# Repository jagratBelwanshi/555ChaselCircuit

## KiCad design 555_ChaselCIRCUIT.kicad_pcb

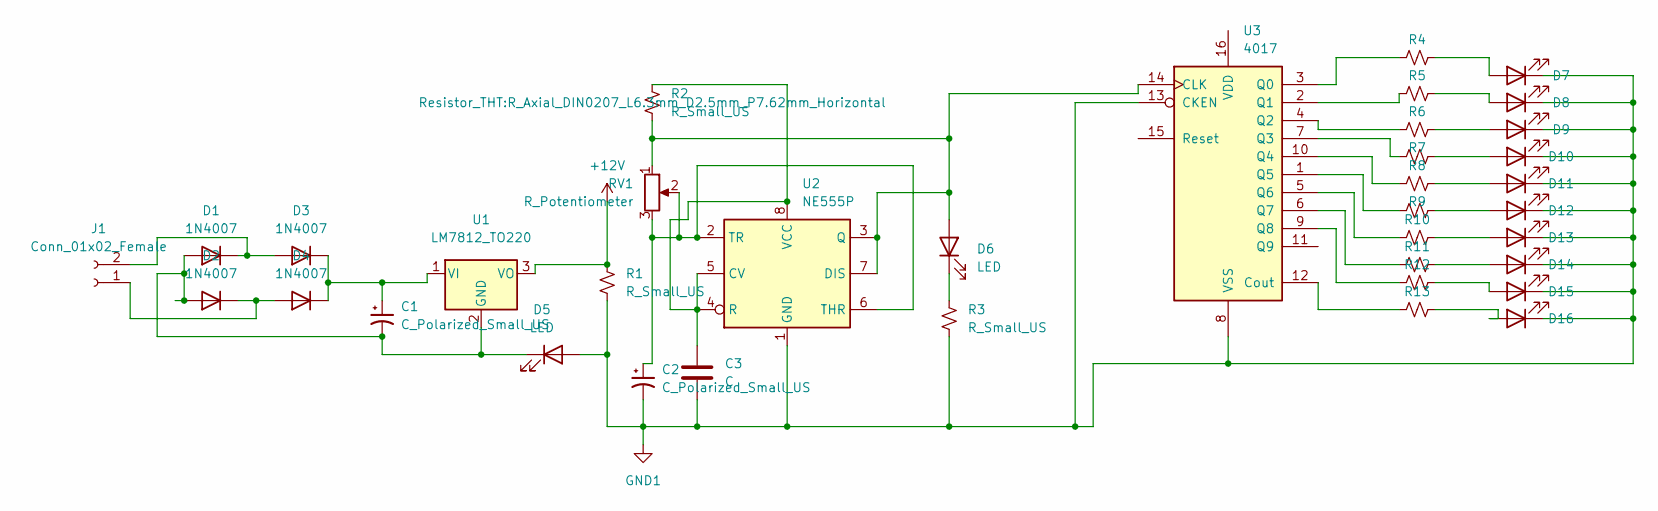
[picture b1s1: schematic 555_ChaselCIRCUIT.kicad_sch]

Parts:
C1: C_Polarized_Small_US
C2: C_Polarized_Small_US; CP_Radial_D8.0mm_P2.50mm
C3: C
D1, D2, D3, D4: 1N4007; D_DO-41_SOD81_P10.16mm_Horizontal
D5, D7, D8, D9, D10, D11, D12, D13, D14: LED; LED_D4.0mm
D6, D15, D16: LED
J1: Conn_01x02_Female
R1, R12: R_Small_US; R_Axial_DIN0204_L3.6mm_D1.6mm_P7.62mm_Horizontal
R2, R3: R_Small_US; R_Axial_DIN0207_L6.3mm_D2.5mm_P7.62mm_Horizontal
R4, R5, R6, R7, R8, R9, R10, R11, R13: R_Small_US
RV1: R_Potentiometer
U1: LM7812_TO220; TO-220-3_Vertical
U2: NE555P; DIP-8_W7.62mm
U3: 4017

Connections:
+12V: R1.1, U1.3 (VO)
GND1: C2.2, C3.2, D5.2 (A), D7.1 (K), D8.1 (K), D9.1 (K), D10.1 (K), D11.1 (K), D12.1 (K), D13.1 (K), D14.1 (K), D15.1 (K), D16.1 (K), R1.2, R3.2, U2.1 (GND), U3.8 (VSS), U3.13 (CKEN)
unnamed: C1.1, D3.1 (K), D4.1 (K), U1.1 (VI)
unnamed: C1.2, D1.2 (A), D2.2 (A), D5.1 (K), U1.2 (GND)
unnamed: C2.1, RV1.2, RV1.3, U2.2 (TR), U2.6 (THR)
unnamed: C3.1, R2.1, U2.4 (R), U2.5 (CV), U2.8 (VCC)
unnamed: D1.1 (K), D3.2 (A), J1.2
unnamed: D2.1 (K), D4.2 (A), J1.1
unnamed: D6.1 (K), R3.1
unnamed: D6.2 (A), R2.2, RV1.1, U2.3 (Q), U2.7 (DIS), U3.14 (CLK)
unnamed: D7.2 (A), R4.2
unnamed: D8.2 (A), R5.2
unnamed: D9.2 (A), R6.2
unnamed: D10.2 (A), R7.2
unnamed: D11.2 (A), R8.2
unnamed: D12.2 (A), R9.2
unnamed: D13.2 (A), R10.2
unnamed: D14.2 (A), R11.2
unnamed: D15.2 (A), R12.2
unnamed: D16.2 (A), R13.2
unnamed: R4.1, U3.3 (Q0)
unnamed: R5.1, U3.2 (Q1)
unnamed: R6.1, U3.4 (Q2)
unnamed: R7.1, U3.7 (Q3)
unnamed: R8.1, U3.10 (Q4)
unnamed: R9.1, U3.1 (Q5)
unnamed: R10.1, U3.5 (Q6)
unnamed: R11.1, U3.6 (Q7)
unnamed: R12.1, U3.9 (Q8)
unnamed: R13.1, U3.12 (Cout)

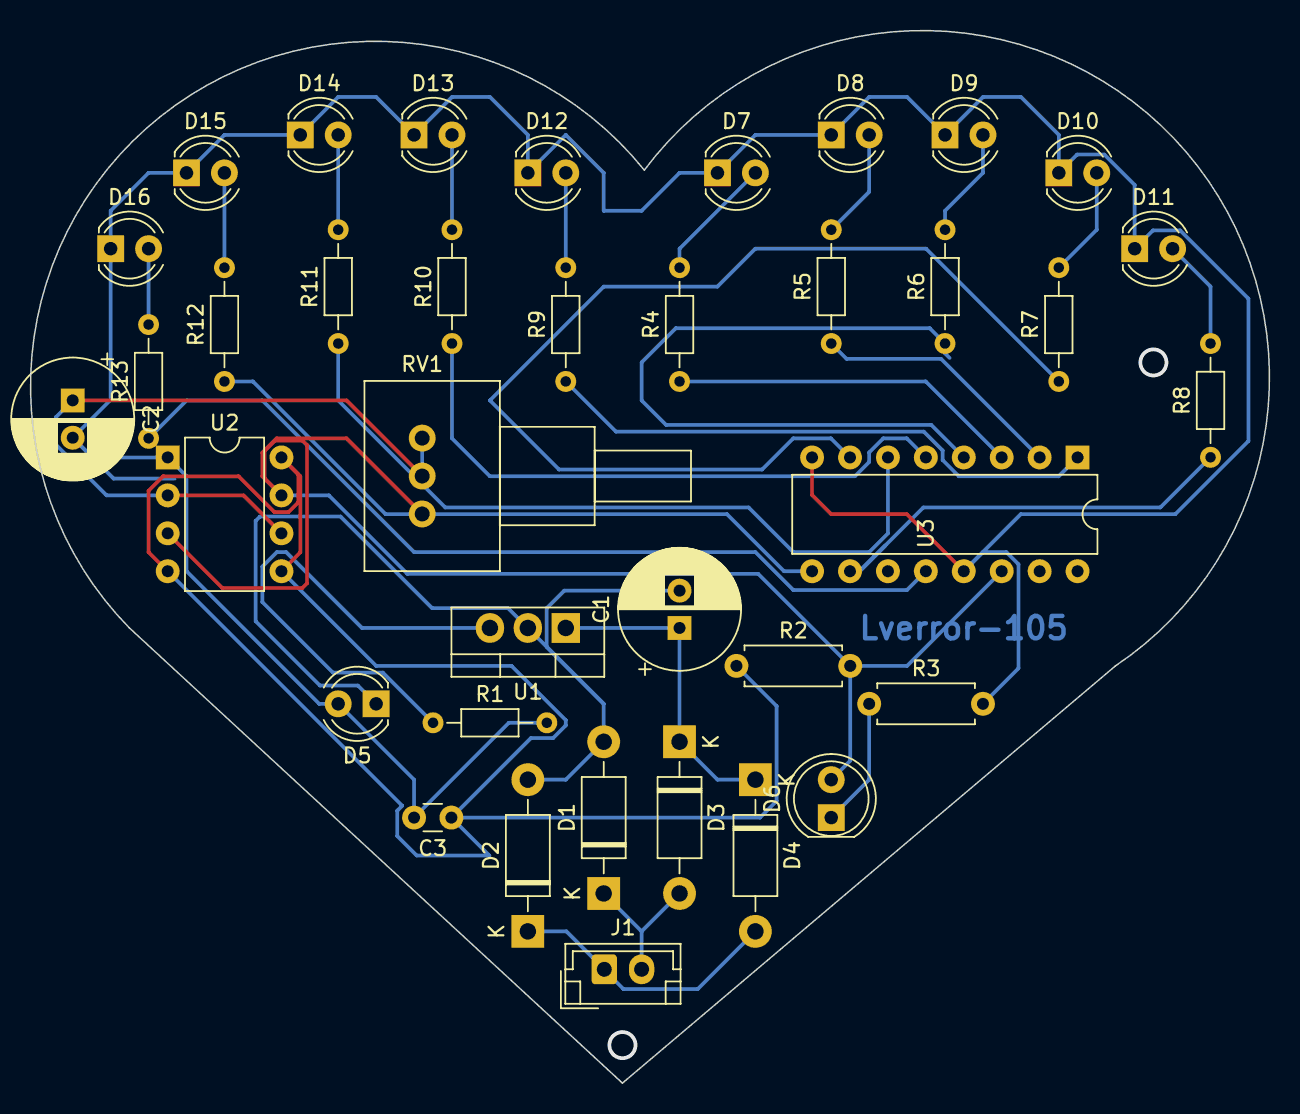
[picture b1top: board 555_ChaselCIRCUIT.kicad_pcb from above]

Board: 2 copper layers, 83.0 x 70.5 mm, 37 parts (0 on the bottom side), 30 nets.

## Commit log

2025-05-20 completeProjectUpload
